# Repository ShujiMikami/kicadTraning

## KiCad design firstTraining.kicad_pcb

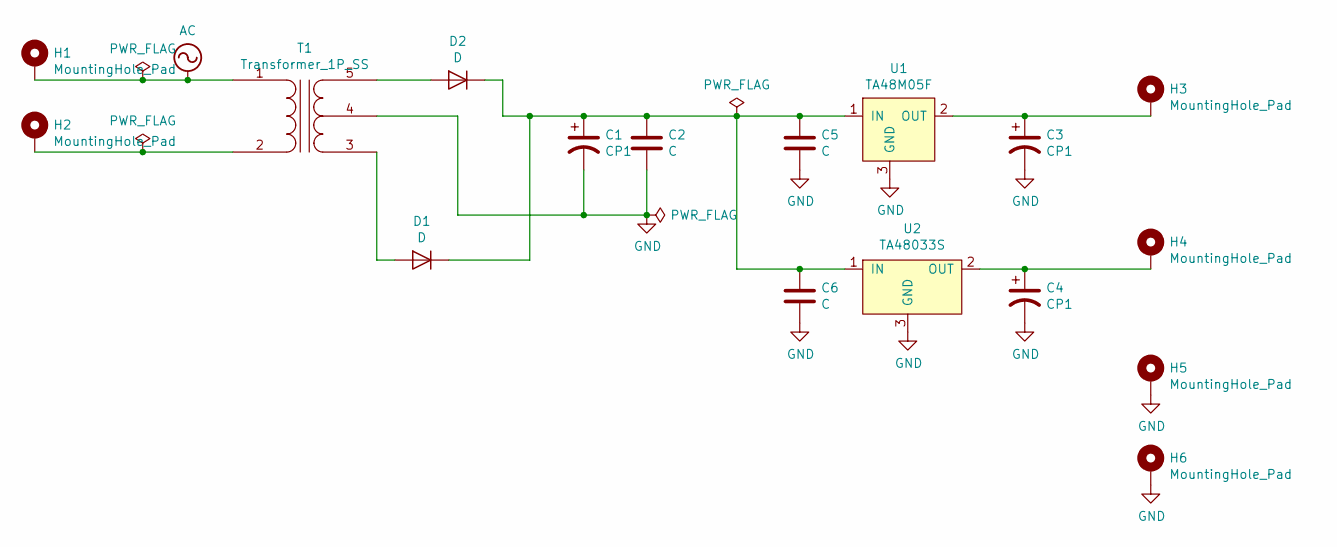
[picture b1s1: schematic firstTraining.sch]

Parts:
C1: CP1; CP_Radial_D18.0mm_P7.50mm
C2, C5, C6: C; C_Disc_D3.0mm_W1.6mm_P2.50mm
C3, C4: CP1; CP_Radial_D5.0mm_P2.00mm
D1, D2: D; D_A-405_P7.62mm_Horizontal
H1, H2: MountingHole_Pad; MountingHole_4.5mm_Pad_Via
H3, H4, H5, H6: MountingHole_Pad; PinHeader_1x01_P2.54mm_Horizontal
T1: Transformer_1P_SS; HP-098
U1: TA48M05F; TOSHIBA_DIP_Regulators
U2: TA48033S; TOSHIBA_DIP_Regulators

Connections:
AC: H1.1, T1.1 (AA)
GND: C1.2, C2.2, C3.2, C4.2, C5.2, C6.2, H5.1, H6.1, T1.4 (SC), U1.3 (GND), U2.3 (GND)
unnamed: C1.1, C2.1, C5.1, C6.1, D1.1 (K), D2.1 (K), U1.1 (IN), U2.1 (IN)
unnamed: C3.1, H3.1, U1.2 (OUT)
unnamed: C4.1, H4.1, U2.2 (OUT)
unnamed: D1.2 (A), T1.3 (SA)
unnamed: D2.2 (A), T1.5 (SB)
unnamed: H2.1, T1.2 (AB)

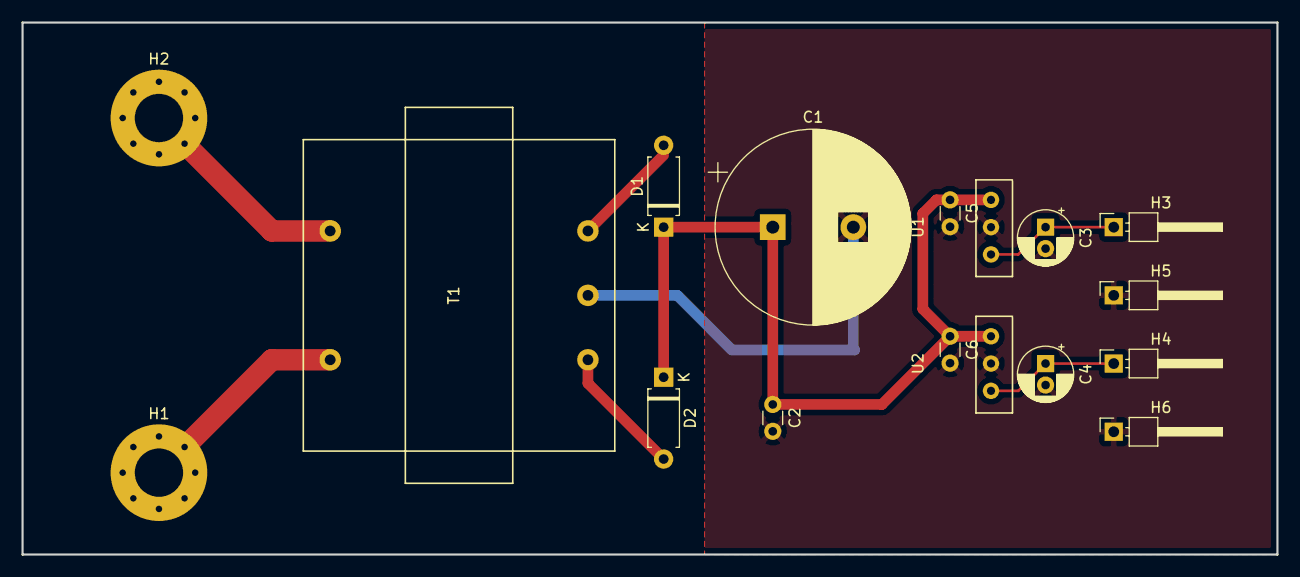
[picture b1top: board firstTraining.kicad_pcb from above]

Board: 2 copper layers, 116.8 x 49.5 mm, 17 parts (0 on the bottom side), 8 nets.

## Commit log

2018-10-29 配線した
2018-10-29 部品の場所を再配置
2018-10-29 バックアップファイルを無視
2018-10-29 3V3電源を追加
2018-10-29 アノテーションとERC実行
2018-10-29 フットプリント設定, トランスはフットプリント要作成
2018-10-30 センタータップ式に修正
2018-10-30 フットプリント再実施
2018-10-30 トランスのフットプリント作成, フットプリント指定
2018-10-30 ネットリスト作成
2018-10-30 schが保存されていなかった
2018-10-30 レギュレータ部品を新たに作成
2018-10-30 GND配線の番号付与追加, 配置実施
2018-10-31 パターン配線
2018-10-31 GNDベタ
2018-10-31 マウンティングホールを作成
2018-10-31 スルホとピンヘッダ設定
2018-10-31 ネットリスト更新
2018-10-31 パターン状にビアを追加
2018-10-31 GNDビアを追加
2018-10-31 GNDパッドに変更
2018-10-31 pcbのgndベタを修正
2018-10-31 原点を追加
2018-10-31 ガーバーデータを排出
2018-10-31 ファイル名をElecrow仕様に合わせて修正
2018-10-31 Zip圧縮
2018-10-31 Elecrowの最大寸法に入れた
2018-10-31 ガーバーを更新
2018-11-17 ボードの仕上がりレポート作成
2018-11-17 レギュレータのコンデンサを入れ替え
2018-11-17 ネットリストを更新
2018-11-17 フットプリントとネットリスト更新
2018-11-17 レギュレータフットプリントを追加
2018-11-17 レギュレータのフットプリントを構成
2018-11-17 フットプリント更新した
2018-11-17 NETリスト更新, PCB図面新規作成
2018-11-17 PCBを一部配線
2018-11-17 GNDベタを追加
2018-11-18 高電圧部分の太さを修正
2018-11-18 ドリル原点指定
2018-11-18 エッジカットのレイヤーに変更
2018-11-18 ベタパターンを修正
2018-11-18 ガーバーファイルを生成
